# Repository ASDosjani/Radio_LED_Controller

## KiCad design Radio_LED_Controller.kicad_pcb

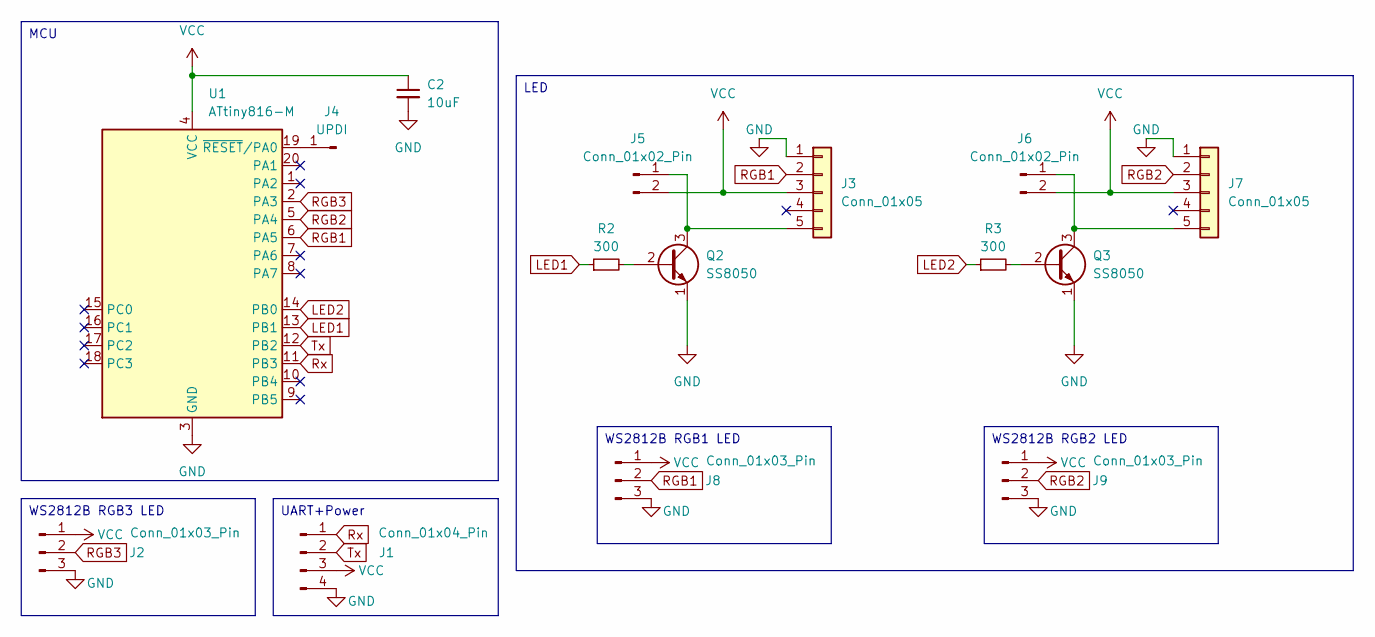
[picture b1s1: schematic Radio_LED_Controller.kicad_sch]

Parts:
C2: 10uF; C_0603_1608Metric_Pad1.08x0.95mm_HandSolder
J1: Conn_01x04_Pin; SolderPad_01x04_1.5mm
J2, J8, J9: Conn_01x03_Pin; SolderPad_01x03_1.5mm
J3, J7: Conn_01x05; Molex_PicoBlade_53261-0571_1x05-1MP_P1.25mm_Horizontal
J4: UPDI; SolderPad_01x01_1.2mm
J5, J6: Conn_01x02_Pin; SolderPad_01x02_1.5mm
Q2, Q3: SS8050; SOT-23 SS8050
R2, R3: 300; R_0603_1608Metric_Pad0.98x0.95mm_HandSolder
U1: ATtiny816-M; VQFN-20-1EP_3x3mm_P0.4mm_EP1.7x1.7mm

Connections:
GND: C2.2, J1.4, J2.3, J3.1, J7.1, J8.3, J9.3, Q2.1 (E), Q3.1 (E), U1.3 (GND), U1.21 (GND)
LED1: R2.1, U1.13 (PB1)
LED2: R3.1, U1.14 (PB0)
unnamed: J3.5, J5.1, Q2.3 (C)
unnamed: J4.1, U1.19 (~RESET/PA0)
unnamed: J6.1, J7.5, Q3.3 (C)
unnamed: Q2.2 (B), R2.2
unnamed: Q3.2 (B), R3.2
RGB1: J3.2, J8.2, U1.6 (PA5)
RGB2: J7.2, J9.2, U1.5 (PA4)
RGB3: J2.2, U1.2 (PA3)
Rx: J1.1, U1.11 (PB3)
Tx: J1.2, U1.12 (PB2)
VCC: C2.1, J1.3, J2.1, J3.3, J5.2, J6.2, J7.3, J8.1, J9.1, U1.4 (VCC)

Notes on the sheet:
LED
MCU
WS2812B RGB2 LED
UART+Power
WS2812B RGB1 LED
WS2812B RGB3 LED

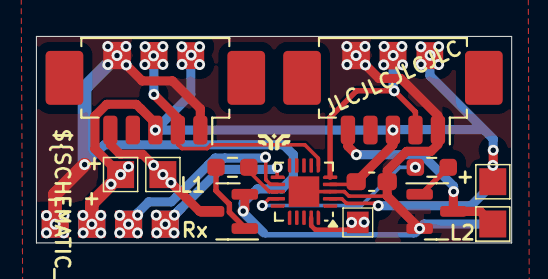
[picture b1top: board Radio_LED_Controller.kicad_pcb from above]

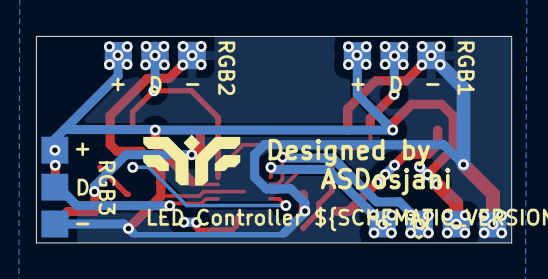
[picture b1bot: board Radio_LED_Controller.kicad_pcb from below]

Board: 2 copper layers, 26.4 x 11.5 mm, 15 parts (3 on the bottom side), 14 nets.

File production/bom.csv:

Designator,Footprint,Quantity,Value,LCSC Part #
C2,0603,1,10uF,
J1,SolderPad_01x04_1.5mm,1,Conn_01x04_Pin,
"J2, J8, J9",SolderPad_01x03_1.5mm,3,Conn_01x03_Pin,
"J3, J7",Molex_PicoBlade_53261-0571_1x05-1MP_P1.25mm_Horizontal,2,Conn_01x05,
J4,SolderPad_01x01_1.2mm,1,UPDI,
"J5, J6",SolderPad_01x02_1.5mm,2,Conn_01x02_Pin,
"Q2, Q3",SOT-23 SS8050,2,SS8050,
"R2, R3",0603,2,300,
U1,VQFN-20-1EP_3x3mm_P0.4mm_EP1.7x1.7mm,1,ATtiny816-M,

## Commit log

2025-03-21 v0.1
2025-03-27 extra 2 RGB port
2025-04-17 new mcu footprint, zip
2025-04-22 v0.2
2025-05-13 v0.3 - vias for stronger pads
